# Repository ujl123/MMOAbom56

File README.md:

# MMOAbom56
WIP board for the MMOAbom56, a board ostensibly for playing mmo games.
The board technically works as-is, but build at your own risk and all that.

Followed the guide on https://flatfootfox.com/ergogen-introduction/ and was able to complete this in a few hours , well written guide with a lot of details.

If you do want to fab and print this ...  
The pcb files can be found in MMOAbom56/pcbs/gerber/.   
The stl files for is in MMOAbom56/case/  
The (vial) firmware can be found in firmware/compiled  

You will also need

1x rp2040 pro micro mcu (the firmware assumes rp2040, if not you will need to edit the pins to atmega pin names)  
2x male header sockets
2x female header sockets
7x flat m2 screw
7x m2 threaded inserts
56x chocv1 switches of your choice  
56x chocv1 keycaps  
56x chocv1 hotswap sockets  
56x 1N4148 smd diode (through hole) or 1N4148 SOD-123 (smd)
1x (optional) reset butto (find a small one as the gap between the case and pcb is very small.)

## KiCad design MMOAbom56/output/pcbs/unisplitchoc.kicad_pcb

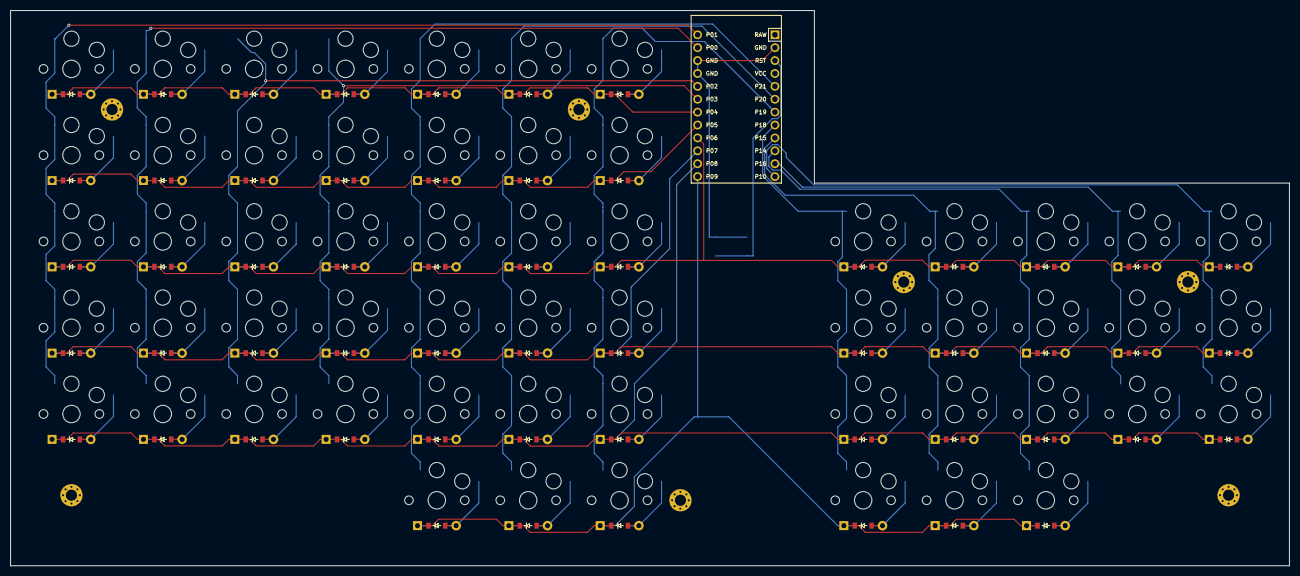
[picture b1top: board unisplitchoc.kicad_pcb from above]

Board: 2 copper layers, 252.0 x 109.4 mm, 121 parts (0 on the bottom side), 76 nets.

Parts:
B1: SW_TACT_ALPS_SKQGABE010
D1, D2, D3, D4, D5, D6, D7, D8, D9, D10, D11, D12, D13, D14, D15, D16, D17, D18, D19, D20, D21, D22, D23, D24, D25, D26, D27, D28, D29, D30, D31, D32, D33, D34, D35, D36, D37, D38, D39, D40, D41, D42, D43, D44, D45, D46, D47, D48, D49, D50, D51, D52, D53, D54, D55, D56: ComboDiode
MCU1: ProMicro
S1, S2, S3, S4, S5, S6, S7, S8, S9, S10, S11, S12, S13, S14, S15, S16, S17, S18, S19, S20, S21, S22, S23, S24, S25, S26, S27, S28, S29, S30, S31, S32, S33, S34, S35, S36, S37, S38, S39, S40, S41, S42, S43, S44, S45, S46, S47, S48, S49, S50, S51, S52, S53, S54, S55, S56: PG1350
_1, _2, _3, _4, _5, _6, _7: MountingHole_2.2mm_M2_Pad_Via

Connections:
GND: B1.1, MCU1.2, MCU1.15, MCU1.16
P0: MCU1.14, S6.1, S7.1, S8.1, S9.1, S10.1
P1: MCU1.13, S1.1, S2.1, S3.1, S4.1, S5.1
P2: MCU1.17, S11.1, S12.1, S13.1, S14.1, S15.1
P3: MCU1.18, S16.1, S17.1, S18.1, S19.1, S20.1
P4: D5.1, D10.1, D15.1, D20.1, D26.1, D32.1, D38.1, MCU1.19
P5: D4.1, D9.1, D14.1, D19.1, D25.1, D31.1, D37.1, MCU1.20
P6: D3.1, D8.1, D13.1, D18.1, D24.1, D30.1, D36.1, D42.1, D46.1, D50.1, D53.1, D56.1, MCU1.21
P7: D2.1, D7.1, D12.1, D17.1, D23.1, D29.1, D35.1, D41.1, D45.1, D49.1, D52.1, D55.1, MCU1.22
P8: D1.1, D6.1, D11.1, D16.1, D22.1, D28.1, D34.1, D40.1, D44.1, D48.1, D51.1, D54.1, MCU1.23
P9: D21.1, D27.1, D33.1, D39.1, D43.1, D47.1, MCU1.24
P10: MCU1.12, S54.1, S55.1, S56.1
P14: MCU1.10, S47.1, S48.1, S49.1, S50.1
P15: MCU1.9, S43.1, S44.1, S45.1, S46.1
P16: MCU1.11, S51.1, S52.1, S53.1
P18: MCU1.8, S39.1, S40.1, S41.1, S42.1
P19: MCU1.7, S33.1, S34.1, S35.1, S36.1, S37.1, S38.1
P20: MCU1.6, S27.1, S28.1, S29.1, S30.1, S31.1, S32.1
P21: MCU1.5, S21.1, S22.1, S23.1, S24.1, S25.1, S26.1
RST: B1.2, MCU1.3
lindex_bottom: D28.2, S28.2
lindex_function: D32.2, S32.2
lindex_home: D29.2, S29.2
lindex_mod: D27.2, S27.2
lindex_num: D31.2, S31.2
lindex_top: D30.2, S30.2
linner_bottom: D34.2, S34.2
linner_function: D38.2, S38.2
linner_home: D35.2, S35.2
linner_mod: D33.2, S33.2
linner_num: D37.2, S37.2
linner_top: D36.2, S36.2
lmacro_bottom: D1.2, S1.2
lmacro_function: D5.2, S5.2
lmacro_home: D2.2, S2.2
lmacro_num: D4.2, S4.2
lmacro_top: D3.2, S3.2
lmiddle_bottom: D22.2, S22.2
lmiddle_function: D26.2, S26.2
lmiddle_home: D23.2, S23.2
lmiddle_mod: D21.2, S21.2
lmiddle_num: D25.2, S25.2
lmiddle_top: D24.2, S24.2
louter_bottom: D6.2, S6.2
louter_function: D10.2, S10.2
louter_home: D7.2, S7.2
louter_num: D9.2, S9.2
louter_top: D8.2, S8.2
lpinky_bottom: D11.2, S11.2
lpinky_function: D15.2, S15.2
lpinky_home: D12.2, S12.2
lpinky_num: D14.2, S14.2
lpinky_top: D13.2, S13.2
lring_bottom: D16.2, S16.2
lring_function: D20.2, S20.2
lring_home: D17.2, S17.2
lring_num: D19.2, S19.2
lring_top: D18.2, S18.2
rindex_bottom: D44.2, S44.2
rindex_home: D45.2, S45.2
rindex_mod: D43.2, S43.2
rindex_top: D46.2, S46.2
rinner_bottom: D40.2, S40.2
rinner_home: D41.2, S41.2
rinner_mod: D39.2, S39.2
rinner_top: D42.2, S42.2
rmiddle_bottom: D48.2, S48.2
rmiddle_home: D49.2, S49.2
rmiddle_mod: D47.2, S47.2
rmiddle_top: D50.2, S50.2
rpinky_bottom: D54.2, S54.2
rpinky_home: D55.2, S55.2
rpinky_top: D56.2, S56.2
rring_bottom: D51.2, S51.2
rring_home: D52.2, S52.2
rring_top: D53.2, S53.2

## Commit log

2024-08-04 Add files via upload
    Ergogen configs and outputs for MMOAbom56
2024-08-04 gerber files for pcb fabs
    gerber files for pcb fabs, zip these up and upload into your pcb fab of choice
2024-08-04 source of vial firmware
2024-08-04 firmware, source
2024-08-04 compiled firmware
